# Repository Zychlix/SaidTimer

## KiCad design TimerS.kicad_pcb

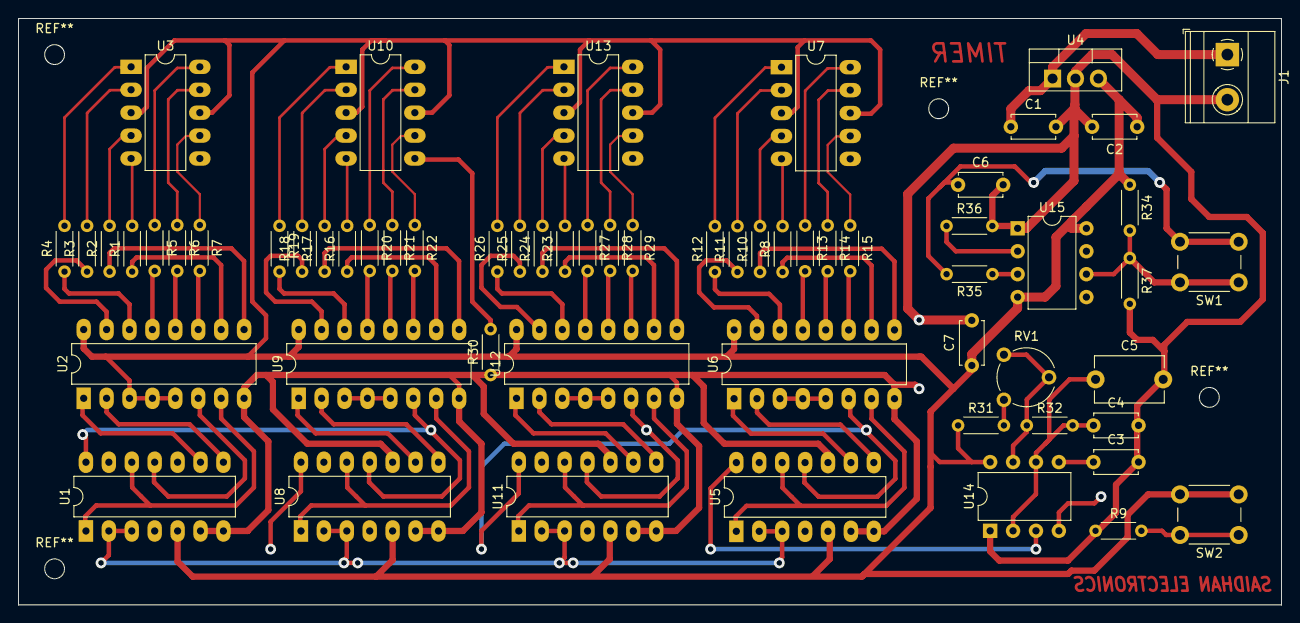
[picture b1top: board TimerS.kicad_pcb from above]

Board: 2 copper layers, 140.0 x 65.0 mm, 62 parts (0 on the bottom side), 85 nets.

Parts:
C1, C2, C3: 10n; C_Disc_D4.7mm_W2.5mm_P5.00mm
C4: 47n; C_Disc_D4.7mm_W2.5mm_P5.00mm
C5: 470n; C_Disc_D7.5mm_W5.0mm_P7.50mm
C6: 470n; C_Disc_D4.7mm_W2.5mm_P5.00mm
C7: 1u; C_Disc_D4.7mm_W2.5mm_P5.00mm
J1: Power; TerminalBlock_Phoenix_MKDS-1,5-2_1x02_P5.00mm_Horizontal
R1, R2, R3, R4, R5, R6, R7, R8, R9, R10, R11, R12, R13, R14, R15, R16, R17, R18, R19, R20, R21, R22, R23, R24, R25, R26, R27, R28, R29, R30: 1k; R_Axial_DIN0204_L3.6mm_D1.6mm_P5.08mm_Horizontal
R31, R32, R34, R35, R36, R37: 100k; R_Axial_DIN0204_L3.6mm_D1.6mm_P5.08mm_Horizontal
RV1: R_Potentiometer; Potentiometer_Piher_PT-6-V_Vertical
SW1: Start/Stop; SW_PUSH_6mm_H5mm
SW2: Reset; SW_PUSH_6mm_H5mm
U1, U5, U8, U11: 74LS90; DIP-14_W7.62mm_LongPads
U2, U6, U9, U12: 74LS47; DIP-16_W7.62mm_LongPads
U3, U7, U10, U13: DIP-10_W7.62mm_LongPads
U4: L7805; TO-220-3_Vertical
U14, U15: NA555P; DIP-8_W7.62mm

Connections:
+5V: C2.1, C7.1, R31.1, R34.1, SW2.2 (B), U1.5 (VCC), U2.3 (LT), U2.4 (BI), U2.5 (RBI), U2.16 (VCC), U3.3 (A), U3.8 (A), U4.3 (OUT), U5.5 (VCC), U6.3 (LT), U6.4 (BI), U6.5 (RBI), U6.16 (VCC), U7.3 (A), U7.8 (A), U8.5 (VCC), U9.3 (LT), U9.4 (BI), U9.5 (RBI), U9.16 (VCC), U10.3 (A), U10.8 (A), U11.5 (VCC), U12.3 (LT), U12.4 (BI), U12.5 (RBI), U12.16 (VCC), U13.3 (A), U13.8 (A), U14.8 (VCC), U15.4 (R), U15.8 (VCC)
/Digit_Section1/CLK_OUT: U5.11 (Q3), U6.6 (D), U11.14 (CP0)
/Digit_Section2/CLK_IN: U8.14 (CP0), U11.11 (Q3), U12.6 (D)
/Digit_Section2/DP: R30.2, U10.6 (dp)
/Digit_Section/CLK_IN: U1.14 (CP0), U8.11 (Q3), U9.6 (D)
/Digit_Section/CLK_OUT: U1.11 (Q3), U2.6 (D)
/Digit_Section/RST: R9.2, SW2.1 (A), U1.2 (R0(1)), U1.3 (R0(2)), U5.2 (R0(1)), U5.3 (R0(2)), U8.2 (R0(1)), U8.3 (R0(2)), U11.2 (R0(1)), U11.3 (R0(2))
CLK: U5.14 (CP0), U14.3 (Q)
GND: C1.2, C2.2, C3.2, C4.2, C5.2, C6.2, C7.2, J1.2, R9.1, R30.1, R36.2, R37.2, U1.6 (R9(1)), U1.7 (R9(2)), U1.10 (GND), U2.8 (GND), U4.2 (GND), U5.6 (R9(1)), U5.7 (R9(2)), U5.10 (GND), U6.8 (GND), U8.6 (R9(1)), U8.7 (R9(2)), U8.10 (GND), U9.8 (GND), U11.6 (R9(1)), U11.7 (R9(2)), U11.10 (GND), U12.8 (GND), U14.1 (GND), U15.1 (GND)
unnamed: C1.1, J1.1, U4.1 (IN)
unnamed: R31.2, RV1.1
unnamed: R34.2, R36.1, R37.1, SW1.1 (A), U15.2 (TR), U15.6 (THR)
unnamed: C6.1, R35.2, SW1.2 (B)
unnamed: U1.1 (CP1..3), U1.12 (Q0), U2.7 (A)
unnamed: U1.9 (Q1), U2.1 (B)
unnamed: U1.8 (Q2), U2.2 (C)
unnamed: R5.2, U2.13 (a)
unnamed: R6.2, U2.12 (b)
unnamed: R7.2, U2.11 (c)
unnamed: R1.1, U2.10 (d)
unnamed: R2.1, U2.9 (e)
unnamed: R3.1, U2.15 (f)
unnamed: R4.1, U2.14 (g)
unnamed: R5.1, U3.10 (a)
unnamed: R6.1, U3.9 (b)
unnamed: R7.1, U3.7 (c)
unnamed: R1.2, U3.5 (d)
unnamed: R2.2, U3.4 (e)
unnamed: R3.2, U3.2 (f)
unnamed: R4.2, U3.1 (g)
unnamed: U5.1 (CP1..3), U5.12 (Q0), U6.7 (A)
unnamed: U5.9 (Q1), U6.1 (B)
unnamed: U5.8 (Q2), U6.2 (C)
unnamed: R13.2, U6.13 (a)
unnamed: R14.2, U6.12 (b)
unnamed: R15.2, U6.11 (c)
unnamed: R8.1, U6.10 (d)
unnamed: R10.1, U6.9 (e)
unnamed: R11.1, U6.15 (f)
unnamed: R12.1, U6.14 (g)
unnamed: R13.1, U7.10 (a)
unnamed: R14.1, U7.9 (b)
unnamed: R15.1, U7.7 (c)
unnamed: R8.2, U7.5 (d)
unnamed: R10.2, U7.4 (e)
unnamed: R11.2, U7.2 (f)
unnamed: R12.2, U7.1 (g)
unnamed: U8.1 (CP1..3), U8.12 (Q0), U9.7 (A)
unnamed: U8.9 (Q1), U9.1 (B)
unnamed: U8.8 (Q2), U9.2 (C)
unnamed: R20.2, U9.13 (a)
unnamed: R21.2, U9.12 (b)
unnamed: R22.2, U9.11 (c)
unnamed: R16.1, U9.10 (d)
unnamed: R17.1, U9.9 (e)
unnamed: R18.1, U9.15 (f)
unnamed: R19.1, U9.14 (g)
unnamed: R20.1, U10.10 (a)
unnamed: R21.1, U10.9 (b)
unnamed: R22.1, U10.7 (c)
unnamed: R16.2, U10.5 (d)
unnamed: R17.2, U10.4 (e)
unnamed: R18.2, U10.2 (f)
unnamed: R19.2, U10.1 (g)
unnamed: U11.1 (CP1..3), U11.12 (Q0), U12.7 (A)
unnamed: U11.9 (Q1), U12.1 (B)
unnamed: U11.8 (Q2), U12.2 (C)
unnamed: R27.2, U12.13 (a)
unnamed: R28.2, U12.12 (b)
unnamed: R29.2, U12.11 (c)
unnamed: R23.1, U12.10 (d)
unnamed: R24.1, U12.9 (e)
unnamed: R25.1, U12.15 (f)
unnamed: R26.1, U12.14 (g)
unnamed: R27.1, U13.10 (a)
unnamed: R28.1, U13.9 (b)
unnamed: R29.1, U13.7 (c)
unnamed: R23.2, U13.5 (d)
unnamed: R24.2, U13.4 (e)
unnamed: R25.2, U13.2 (f)
unnamed: R26.2, U13.1 (g)
unnamed: C3.1, U14.5 (CV)
unnamed: R32.1, RV1.2, RV1.3, U14.7 (DIS)
unnamed: R35.1, U14.4 (R), U15.3 (Q)
unnamed: C4.1, C5.1, R32.2, U14.2 (TR), U14.6 (THR)

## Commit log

2023-11-28 Initial
2023-11-28 Layout correction
2023-11-28 PDF added
2023-11-29 Production
2025-02-24 bckp
